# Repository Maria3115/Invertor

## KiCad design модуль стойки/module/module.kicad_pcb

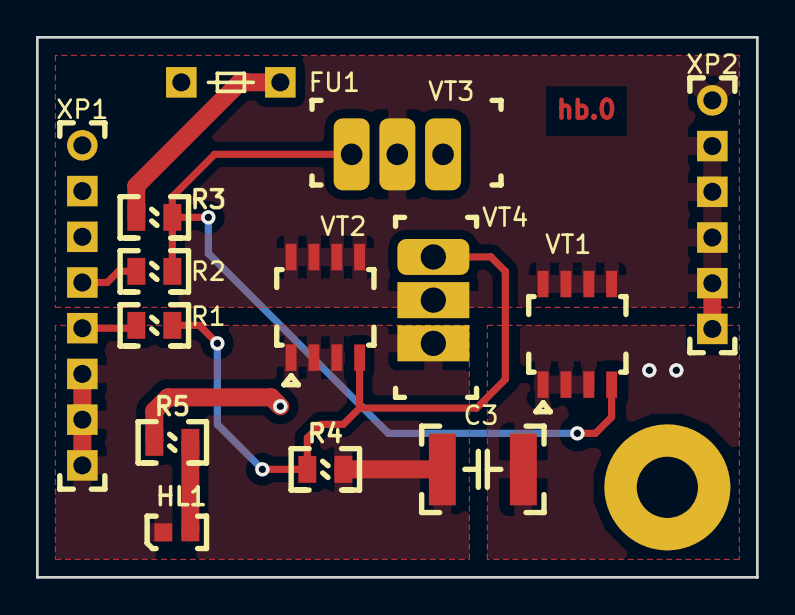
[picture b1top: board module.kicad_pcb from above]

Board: 2 copper layers, 40.0 x 30.0 mm, 15 parts (0 on the bottom side), 9 nets.

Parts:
C3: Конденсатор_керамический; Конденсатор_SMD_1812
FU1: Предохранитель; Предохранитель_MF-R_d10.4
HL1: Светодиод; Светодиод_SMD_0603
R1, R2, R3, R4, R5: Резистор_0,125Вт; Резистор_SMD_0805_0,125Вт
VT1: Транзистор_полевой_P-канал(so-8); SO-8
VT2: Транзистор_полевой_N-канал(so-8); SO-8
VT3: Транзистор_полевой_P-канал; Транзистор_P_IRF9Z24NPBF
VT4: Транзистор_полевой_N-канал; Транзистор_N_STP10NK60Z
XP1: Вилка_PLS8; Вилка_PLS8_вертикальная
XP2: Вилка_PLS6; Вилка_PLS6_вертикальная
rM3: Отверстие_М3

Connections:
unnamed: C3.1, FU1.2, R3.1, R5.1, VT1.1, VT1.2, VT1.3, VT3.3
unnamed: C3.2, HL1.2, R4.2, VT2.1, VT2.2, VT2.3, VT4.3, XP1.6, XP1.7, XP1.8
unnamed: FU1.1, XP1.1, XP1.2, XP1.3
unnamed: HL1.1, R5.2
unnamed: R1.1, XP1.5
unnamed: R1.2, R4.1, VT2.4, VT4.1
unnamed: R2.1, XP1.4
unnamed: R2.2, R3.2, VT1.4, VT3.1
unnamed: VT1.5, VT1.6, VT1.7, VT1.8, VT2.5, VT2.6, VT2.7, VT2.8, VT3.2, VT4.2, XP2.1, XP2.2, XP2.3, XP2.4, XP2.5, XP2.6

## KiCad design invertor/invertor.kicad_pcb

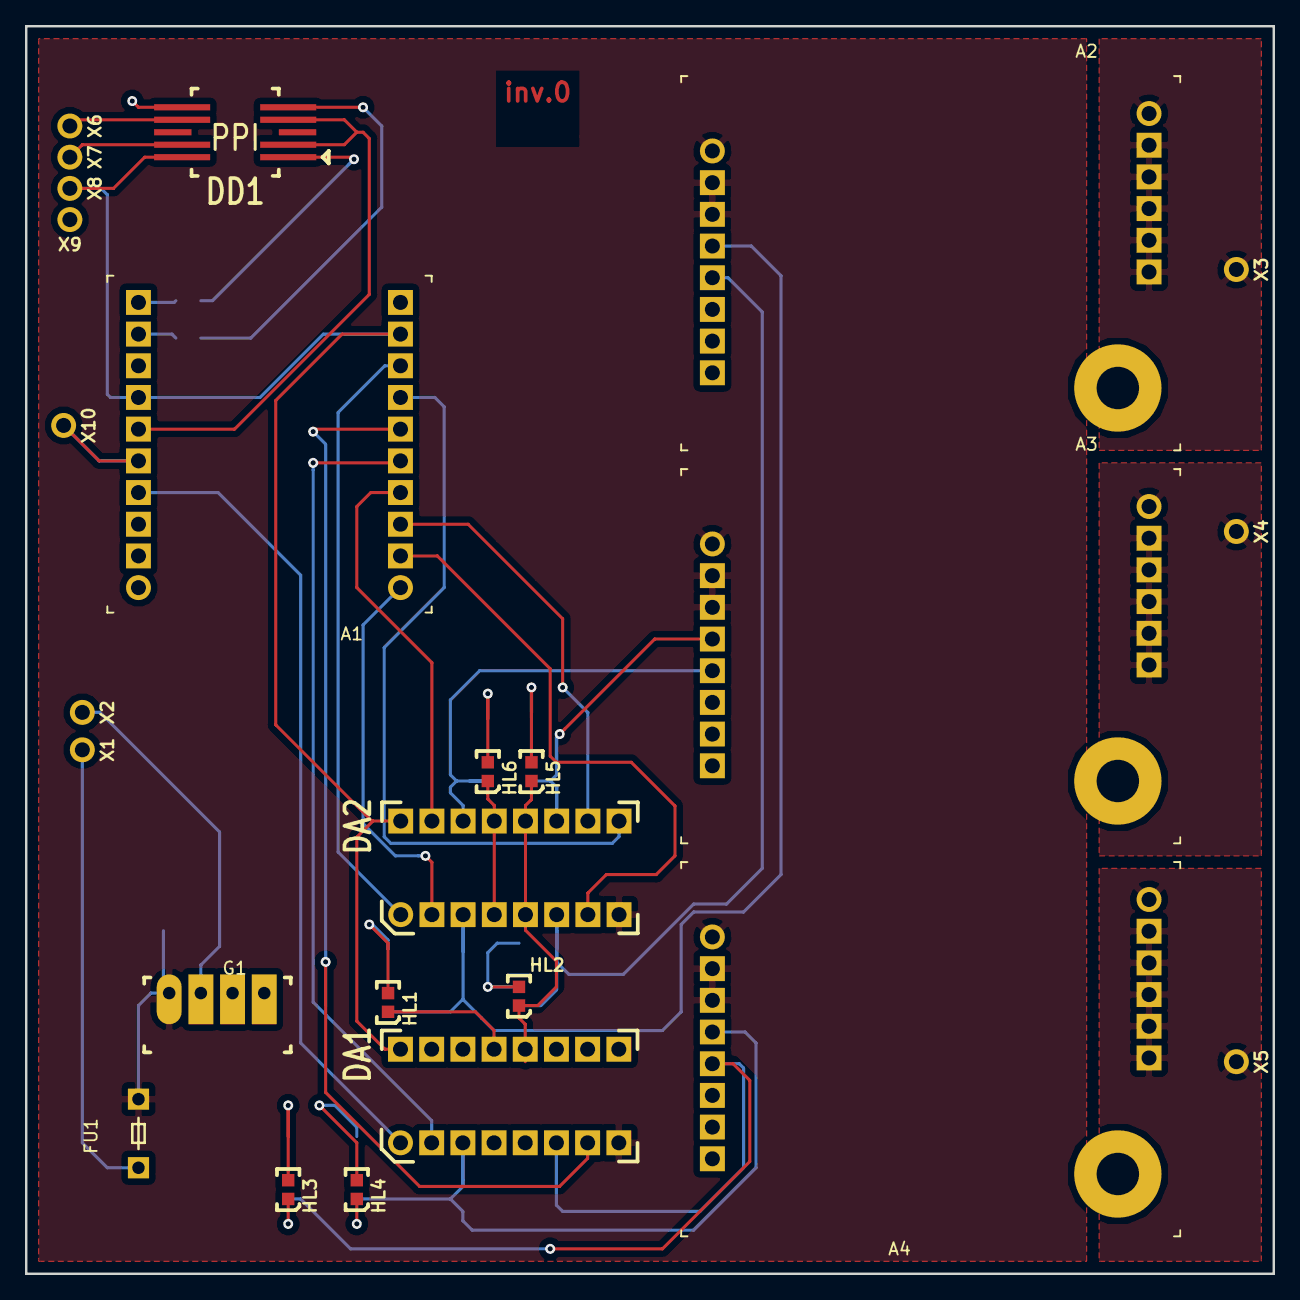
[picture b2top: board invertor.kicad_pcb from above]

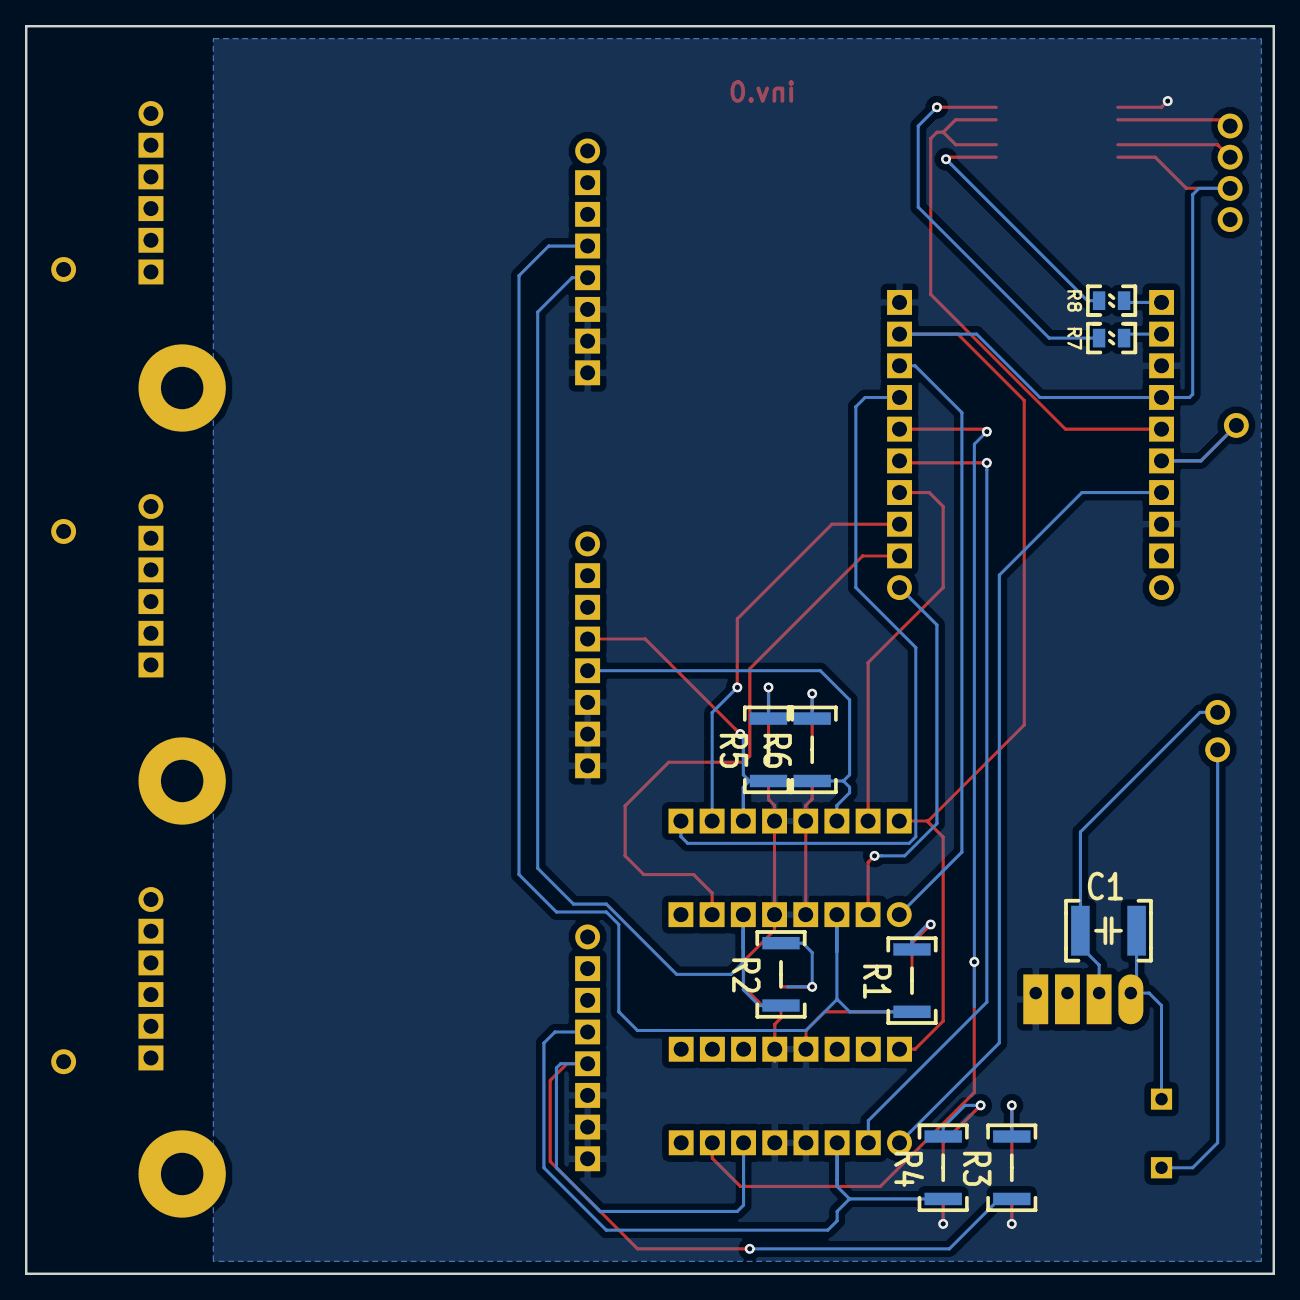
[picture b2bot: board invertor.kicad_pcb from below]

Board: 2 copper layers, 100.0 x 100.0 mm, 34 parts (9 on the bottom side), 37 nets.

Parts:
A1: plata_avr8; avr
A2, A3, A4: Module_halfbridge; module_halfbridge
C1: Конденсатор_керамический; Конденсатор_SMD_1812
DA1, DA2: KP1128KT3; DIP16
DD1: 5559ИН28У; Микросхема_5559ИНхх
FU1: Предохранитель; Предохранитель_MF-R_d10.4
G1: Модульпитания; Модуль_питания_AM1S_Z
HL1, HL2, HL3, HL4, HL5, HL6: Светодиод; Светодиод_SMD_0603
R1, R2, R3, R4, R5, R6: Резистор_0,125Вт; Резистор_SMD_2010-0,5_Вт
R7, R8: Резистор_0,125Вт; Резистор_SMD_0805_0,125Вт
X1: 12В; ОтверстиеD1.2
X2: 0DC; ОтверстиеD1.2
X3, X6: A; ОтверстиеD1.2
X4, X7: B; ОтверстиеD1.2
X5: C; ОтверстиеD1.2
X8: Vcc; ОтверстиеD1.2
X9: gnd; ОтверстиеD1.2
X10: ацп; ОтверстиеD1.2

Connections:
0dc: A1.10, A1.13, A1.18, A2.6, A2.7, A2.8, A3.6, A3.7, A3.8, A4.6, A4.7, A4.8, DA1.4, DA1.5, DA1.12, DA1.13, DA2.4, DA2.5, DA2.12, DA2.13, DD1.5, G1.4, HL1.2, HL2.2, HL3.2, HL4.2, HL5.2, HL6.2
12dc: A2.1, A2.2, A2.3, A3.1, A3.2, A3.3, A4.1, A4.2, A4.3, C1.1, DA1.8, DA2.8, FU1.2, G1.1
K1: A1.1, DA2.2
K2: A1.2, DA2.7
K3: A1.3, DA2.10
K4: A1.4, DA2.15
K5: A1.5, DA1.2
K6: A1.6, DA1.7
unnamed: A1.7, DA2.9
unnamed: A1.8, DA2.1
unnamed: A1.14, DA1.1
unnamed: A1.15, X10.1
unnamed: A2.4, DA2.3, R1.1
unnamed: A2.5, DA2.6, R2.1
unnamed: A2.9, A2.10, A2.11, A2.12, A2.13, A2.14, X3.1
unnamed: A3.4, DA2.11, R5.1
unnamed: A3.5, DA2.14, R6.1
unnamed: A3.9, A3.10, A3.11, A3.12, A3.13, A3.14, X4.1
unnamed: A4.4, DA1.3, R4.1
unnamed: A4.5, DA1.6, R3.1
unnamed: A4.9, A4.10, A4.11, A4.12, A4.13, A4.14, X5.1
unnamed: C1.2, G1.2, X2.1
unnamed: DD1.1, R8.1
unnamed: DD1.4, R7.2
unnamed: DD1.6, X6.1
unnamed: DD1.7, X7.1
unnamed: FU1.1, X1.1
unnamed: HL1.1, R1.2
unnamed: HL2.1, R2.2
unnamed: HL3.1, R3.2
unnamed: HL4.1, R4.2
unnamed: HL5.1, R5.2
unnamed: HL6.1, R6.2
en: A1.16, DD1.2, DD1.3
rx: A1.20, R8.2
tx: A1.19, R7.1
vcc: A1.9, A1.17, DA1.16, DA2.16, DD1.8, X8.1

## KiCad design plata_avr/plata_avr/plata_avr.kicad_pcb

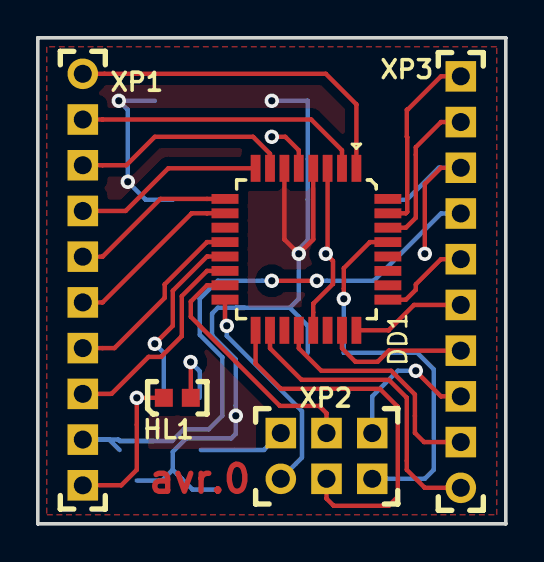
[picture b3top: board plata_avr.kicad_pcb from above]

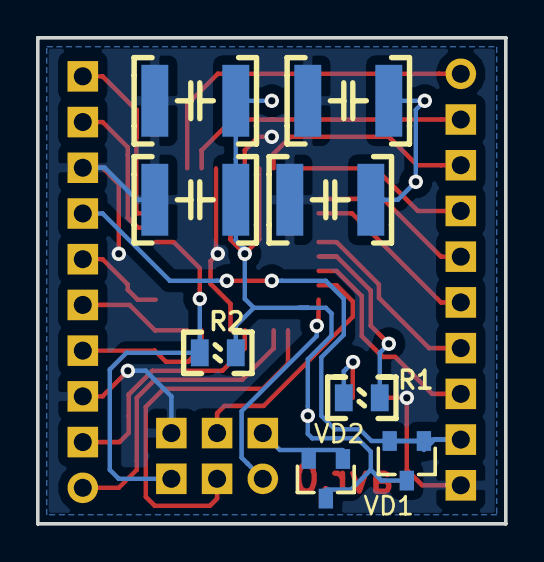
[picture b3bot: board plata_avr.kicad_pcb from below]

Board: 2 copper layers, 26.0 x 27.0 mm, 13 parts (8 on the bottom side), 25 nets.

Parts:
C1, C2, C3, C4: Конденсатор_керамический; Конденсатор_SMD_1812
DD1: ATmega8A-AU; микросхема_ATMEGA-8-161AU
HL1: Светодиод; Светодиод_SMD_0603
R1, R2: Резистор_0,125Вт; Резистор_SMD_0805_0,125Вт
VD1, VD2: Диод_шоттки; Диод_BAR43CFILM_SOT-23
XP1, XP3: Вилка_PLS10; Вилка_PLS10_вертикальная
XP2: Вилка_PLD6_ПРОГ; Вилка_PLD6_вертикальная

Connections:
unnamed: HL1.1, R1.2
unnamed: VD2.1, XP2.2
Ucc: VD1.1, XP1.9, XP3.7
aref: DD1.20, XP3.2
avcc: DD1.18, XP3.1
gnd: C1.2, C2.2, C3.2, C4.2, DD1.3, DD1.5, DD1.21, HL1.2, XP1.10, XP2.6, XP3.3, XP3.8
miso: DD1.16, XP2.1
mosi: DD1.15, XP2.4
pb0: DD1.12, XP1.7
pb1: DD1.13, R1.1
pb2: DD1.14, XP1.8
pb6: DD1.7, XP1.3
pb7: DD1.8, XP1.4
pc0: DD1.23, XP3.4
pc1: DD1.24, XP3.5
pc2: DD1.25, XP3.6
pd3: DD1.1, XP1.1
pd4: DD1.2, XP1.2
pd5: DD1.9, XP1.5
pd6: DD1.10, XP1.6
res: DD1.29, R2.1, XP2.5
rx: DD1.30, XP3.9
sck: DD1.17, XP2.3
tx: DD1.31, XP3.10
vcc: C1.1, C2.1, C3.1, C4.1, DD1.4, DD1.6, R2.2, VD1.2, VD2.2

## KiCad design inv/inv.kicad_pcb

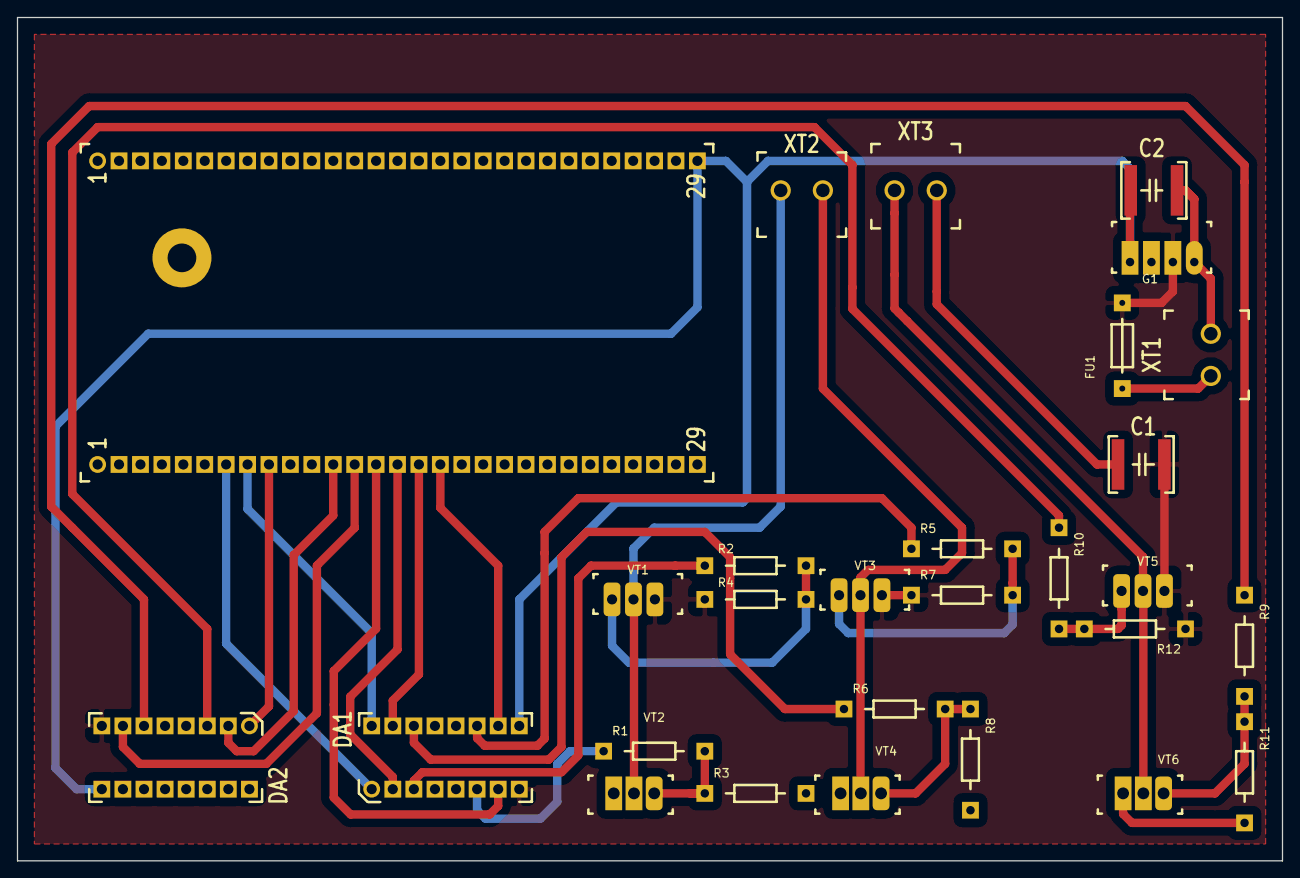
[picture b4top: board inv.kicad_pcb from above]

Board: 2 copper layers, 150.0 x 100.0 mm, 28 parts (0 on the bottom side), 28 nets.

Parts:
A1: Модуль_процессорный_8_бит; Модуль_процессорный_восьмиразрядный
C1, C2: К10-83-50В-1,5мкФ; Конденсатор_SMD_2220
DA1, DA2: KP1128KT3; DIP16
FU1: Предохранитель; Предохранитель_R700
G1: AM1S-Z; Модуль_питания_AM1S_Z
R1, R2, R3, R4, R5, R6, R7, R8, R9, R10, R11, R12: Резистор_0,125Вт; резистор-0,125Вт-DIP
VT1, VT3, VT5: Транзистор_полевой_P-канал; Транзистор_P_IRF9Z24NPBF
VT2, VT4, VT6: Транзистор_полевой_N-канал; Транзистор_N_STP10NK60Z
XT1, XT2, XT3: СКПП-1,0-5Г-2х2(л); Соединитель_СКПП-1,0-5Г-2х2

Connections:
1_E1: A1.7, DA1.1
1_E2: A1.8, DA1.9
1_in1: A1.15, DA1.2
1_in2: A1.14, DA1.7
1_in3: A1.16, DA1.10
1_in4: A1.17, DA1.15
2_E1: A1.9, DA2.1
2_in1: A1.12, DA2.2
2_in2: A1.13, DA2.7
-Vinput: A1.57, C1.1, C2.1, DA1.4, DA1.5, DA1.12, DA1.13, DA2.4, DA2.5, DA2.12, DA2.13, G1.1, G1.3, R3.2, R8.2, R11.2, VT2.3, VT4.3, VT6.3, XT1.2, XT3.2
K1: DA1.3, R2.1
K2: DA1.6, R1.1
K3: DA1.14, R5.1
K4: DA1.11, R6.1
K5: DA2.3, R10.1
K6: DA2.6, R9.1
unnamed: FU1.1, XT1.1
unnamed: R1.2, R3.1, VT2.1
unnamed: R2.2, R4.2, VT1.1
unnamed: R5.2, R7.2, VT3.1
unnamed: R6.2, R8.1, VT4.1
unnamed: R10.2, R12.2, VT5.1
unnamed: R9.2, R11.1, VT6.1
unnamed: VT1.2, VT2.2, XT2.2
unnamed: VT3.2, VT4.2, XT2.1
unnamed: VT5.2, VT6.2, XT3.1
Vcc: A1.58, C2.2, DA1.16, DA2.16, G1.4
Vinput: C1.2, DA1.8, DA2.8, FU1.2, G1.2, R4.1, R7.1, R12.1, VT1.3, VT3.3, VT5.3

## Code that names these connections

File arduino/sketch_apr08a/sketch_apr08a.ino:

#include "C:\el_nikitos\AVR_Lib\mad.h"
byte count = 0;

void setup() {
  // put your setup code here, to run once:
  pinMode(PB0, OUTPUT);
  pinMode(PB2, OUTPUT);
  pinMode(PC0, OUTPUT);
  pinMode(PC1, OUTPUT);

  DDRB |= (1<<6);
  DDRB |= (1<<7);
  pinMode(PD3, OUTPUT);
  pinMode(PD4, OUTPUT);
  
  digitalWrite(PB0, HIGH);
  digitalWrite(PB2, HIGH);
  digitalWrite(PC0, HIGH);
  digitalWrite(PC1, HIGH);
}

void loop() {
  count++;

  PORTB |= (1<<6);
  //pwm(PB6, 20);
  //pwm(PB7, 40);
  pwm(PD3, 60);
  pwm(PD4, 80);
/*
  digitalWrite(PB1, HIGH);
  delay(500);
  digitalWrite(PB1, LOW);
  delay(500);
*/
  if (count>100)
  {
    count = 0;
  }
}

void pwm(byte pin, byte S)
{
  if (count < S)
  {
    digitalWrite(pin, HIGH);
  }
  else
  {
    digitalWrite(pin, LOW);
  }
}

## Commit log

2018-12-18 Статья
2018-12-18 добавлен мапля-файл
    в мапля-файле расписано выражение ia из первого уравнения в системе уравнений
    то же самое повторить для еще 2х уравнений и подставить в последнее уравнени системы
2018-12-19 Мат.модель и презентация
    в презентации тема, в мат.модели доделаны формулы для всех фаз
2018-12-19 Изменена призентация
2018-12-19 добавлен вордик с актуальностью
2018-12-26 создан модуль
2019-01-07 модуль на стадии редактировании
2019-01-07 нет индикации
2019-01-15 модуль стойки - готов
    без индикации
2019-02-07 Платы
2019-02-26 накидал уравнений, пока выводы делать рано
2019-02-26 какие-то удаленные герберы О_о
2019-03-17 Диссертация
2019-03-22 проект в авр студии
2019-03-23 Надо доделать описание мат модели
2019-03-23 добавлены отчеты по Аверину по семестру предыдущему
2019-03-23 схема из matlab
2019-03-27 изменение
2019-04-04 3D стенда
2019-05-07 добавлен скетч-прототип
2019-05-31 скетч для управления инвертором ДПТ
